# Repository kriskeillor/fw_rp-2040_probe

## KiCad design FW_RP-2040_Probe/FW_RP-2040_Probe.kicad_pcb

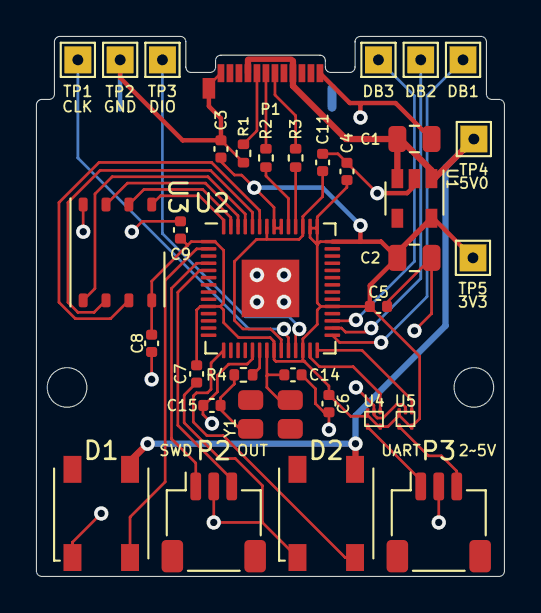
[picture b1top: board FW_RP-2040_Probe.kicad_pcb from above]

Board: 2 copper layers, 26.0 x 30.0 mm, 37 parts (0 on the bottom side), 31 nets.

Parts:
C1, C2: 10uF; C_0805_2012Metric
C3, C4, C5, C6, C7, C8, C9, C11: 10nF; C_0402_1005Metric
C14, C15: 8pF; C_0402_1005Metric
D1, D2: Inolux_IN-PI554FCH; LED_Inolux_IN-PI554FCH_PLCC4_5.0x5.0mm_P3.2mm
DB1, DB2, DB3: TestPoint; TestPoint_Pad_1.5x1.5mm_THT
H1, H2: MountingHole; MountingHole_2.2mm_M2
P1: USB_C_Plug_USB2.0; USB_C_Plug_Molex_105444
P2, P3: JST Female 1x3; JST_SH_SM03B-SRSS-TB_1x03-1MP_P1.00mm_Horizontal
R1: 5.1k; R_0402_1005Metric
R2, R3, R4: 1.2k; R_0402_1005Metric
TP1, TP2, TP3, TP4, TP5: TestPoint; TestPoint_Pad_1.5x1.5mm_THT
U1: AP2112K-3.3; SOT-23-5
U2: RP2040; QFN-56-1EP_7x7mm_P0.4mm_EP3.2x3.2mm
U3: W25Q128JVS; WSON-8-1EP_6x5mm_P1.27mm_EP3.4x4mm
U4, U5: MC74VHC1GT126; SOT−953
Y1: RH100-12.000-9-1015-TR-NS1; 4-SMD_3.2mm-x-2.5mm

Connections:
+1V1: C11.1, U2.23 (DVDD), U2.45 (VREG_VOUT), U2.50 (DVDD)
+3V3: C2.1, C3.1, C4.1, C5.1, C6.1, C7.2, C8.1, C9.1, TP5.1, U1.5 (VOUT), U2.1 (IOVDD), U2.10 (IOVDD), U2.22 (IOVDD), U2.26 (RUN), U2.33 (IOVDD), U2.42 (IOVDD), U2.43 (ADC_AVDD), U2.44 (VREG_IN), U2.48 (USB_VDD), U2.49 (IOVDD), U3.8 (VCC), U4.3 (OE), U4.5 (Vcc), U5.3 (OE), U5.5 (Vcc)
/DEBUG1: DB1.1, U2.29 (GPIO18)
/DEBUG2: DB2.1, U2.30 (GPIO19)
/DEBUG3: DB3.1, U2.31 (GPIO20)
/LED1: D1.2 (DIN), U2.2 (GPIO0)
/LED2: D2.2 (DIN), U2.15 (GPIO12)
/MEM_CLK: U2.52 (QSPI_SCLK), U3.6 (CLK)
/MEM_CS_N: U2.56 (QSPI_SS), U3.1 (~CS)
/MEM_D0: U2.53 (QSPI_SD0), U3.5 (DI(IO0))
/MEM_D1: U2.55 (QSPI_SD1), U3.2 (DO(IO1))
/MEM_D2: U2.54 (QSPI_SD2), U3.3 (IO2)
/MEM_D3: U2.51 (QSPI_SD3), U3.7 (IO3)
/SWCLK_IN: TP1.1, U2.24 (SWCLK)
/SWCLK_OUT: P2.1, U2.4 (GPIO2)
/SWDIO_IN: TP3.1, U2.25 (SWD)
/SWDIO_OUT: P2.3, U2.5 (GPIO3)
/UART_RX: U2.28 (GPIO17), U5.1 (A)
/UART_RX_OUT: P3.3, U5.4 (Y)
/UART_TX: U2.27 (GPIO16), U4.1 (A)
/UART_TX_OUT: P3.1, U4.4 (Y)
/USB_D_N: R3.1, U2.46 (USB_DM)
/USB_D_P: R2.1, U2.47 (USB_DP)
/USB_N: P1.A7 (D-), R3.2
/USB_P: P1.A6 (D+), R2.2
/XI: R4.1, U2.20 (XIN)
/YI: C14.1, U2.21 (XOUT), Y1.3
/YO: C15.1, R4.2, Y1.1
GND: C1.2, C2.2, C3.2, C4.2, C5.2, C6.2, C7.1, C8.2, C9.2, C11.2, C14.2, C15.2, D1.1 (VSS), D2.1 (VSS), P1.A1 (GND), P1.A12 (GND), P1.B1 (GND), P1.B12 (GND), P1.S1 (SHIELD), P2.2, P3.2, R1.2, TP2.1, U1.2 (GND), U2.19 (TESTEN), U2.57 (GND), U3.4 (GND), U4.2 (GND), U5.2 (GND)
unnamed: P1.A5 (CC), R1.1
VBUS: C1.1, D1.3 (VDD), D2.3 (VDD), P1.A4 (VBUS), P1.A9 (VBUS), P1.B4 (VBUS), P1.B9 (VBUS), TP4.1, U1.1 (VIN), U1.3 (EN)

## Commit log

2022-12-20 Add v1.0.2
2022-12-30 Add v1.1.1 schematic and PCB

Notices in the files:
FW_RP-2040_Probe/FW_RP-2040_Probe.kicad_pcb:
This work is licensed under a Creative Commons Attribution 4.0 International License
